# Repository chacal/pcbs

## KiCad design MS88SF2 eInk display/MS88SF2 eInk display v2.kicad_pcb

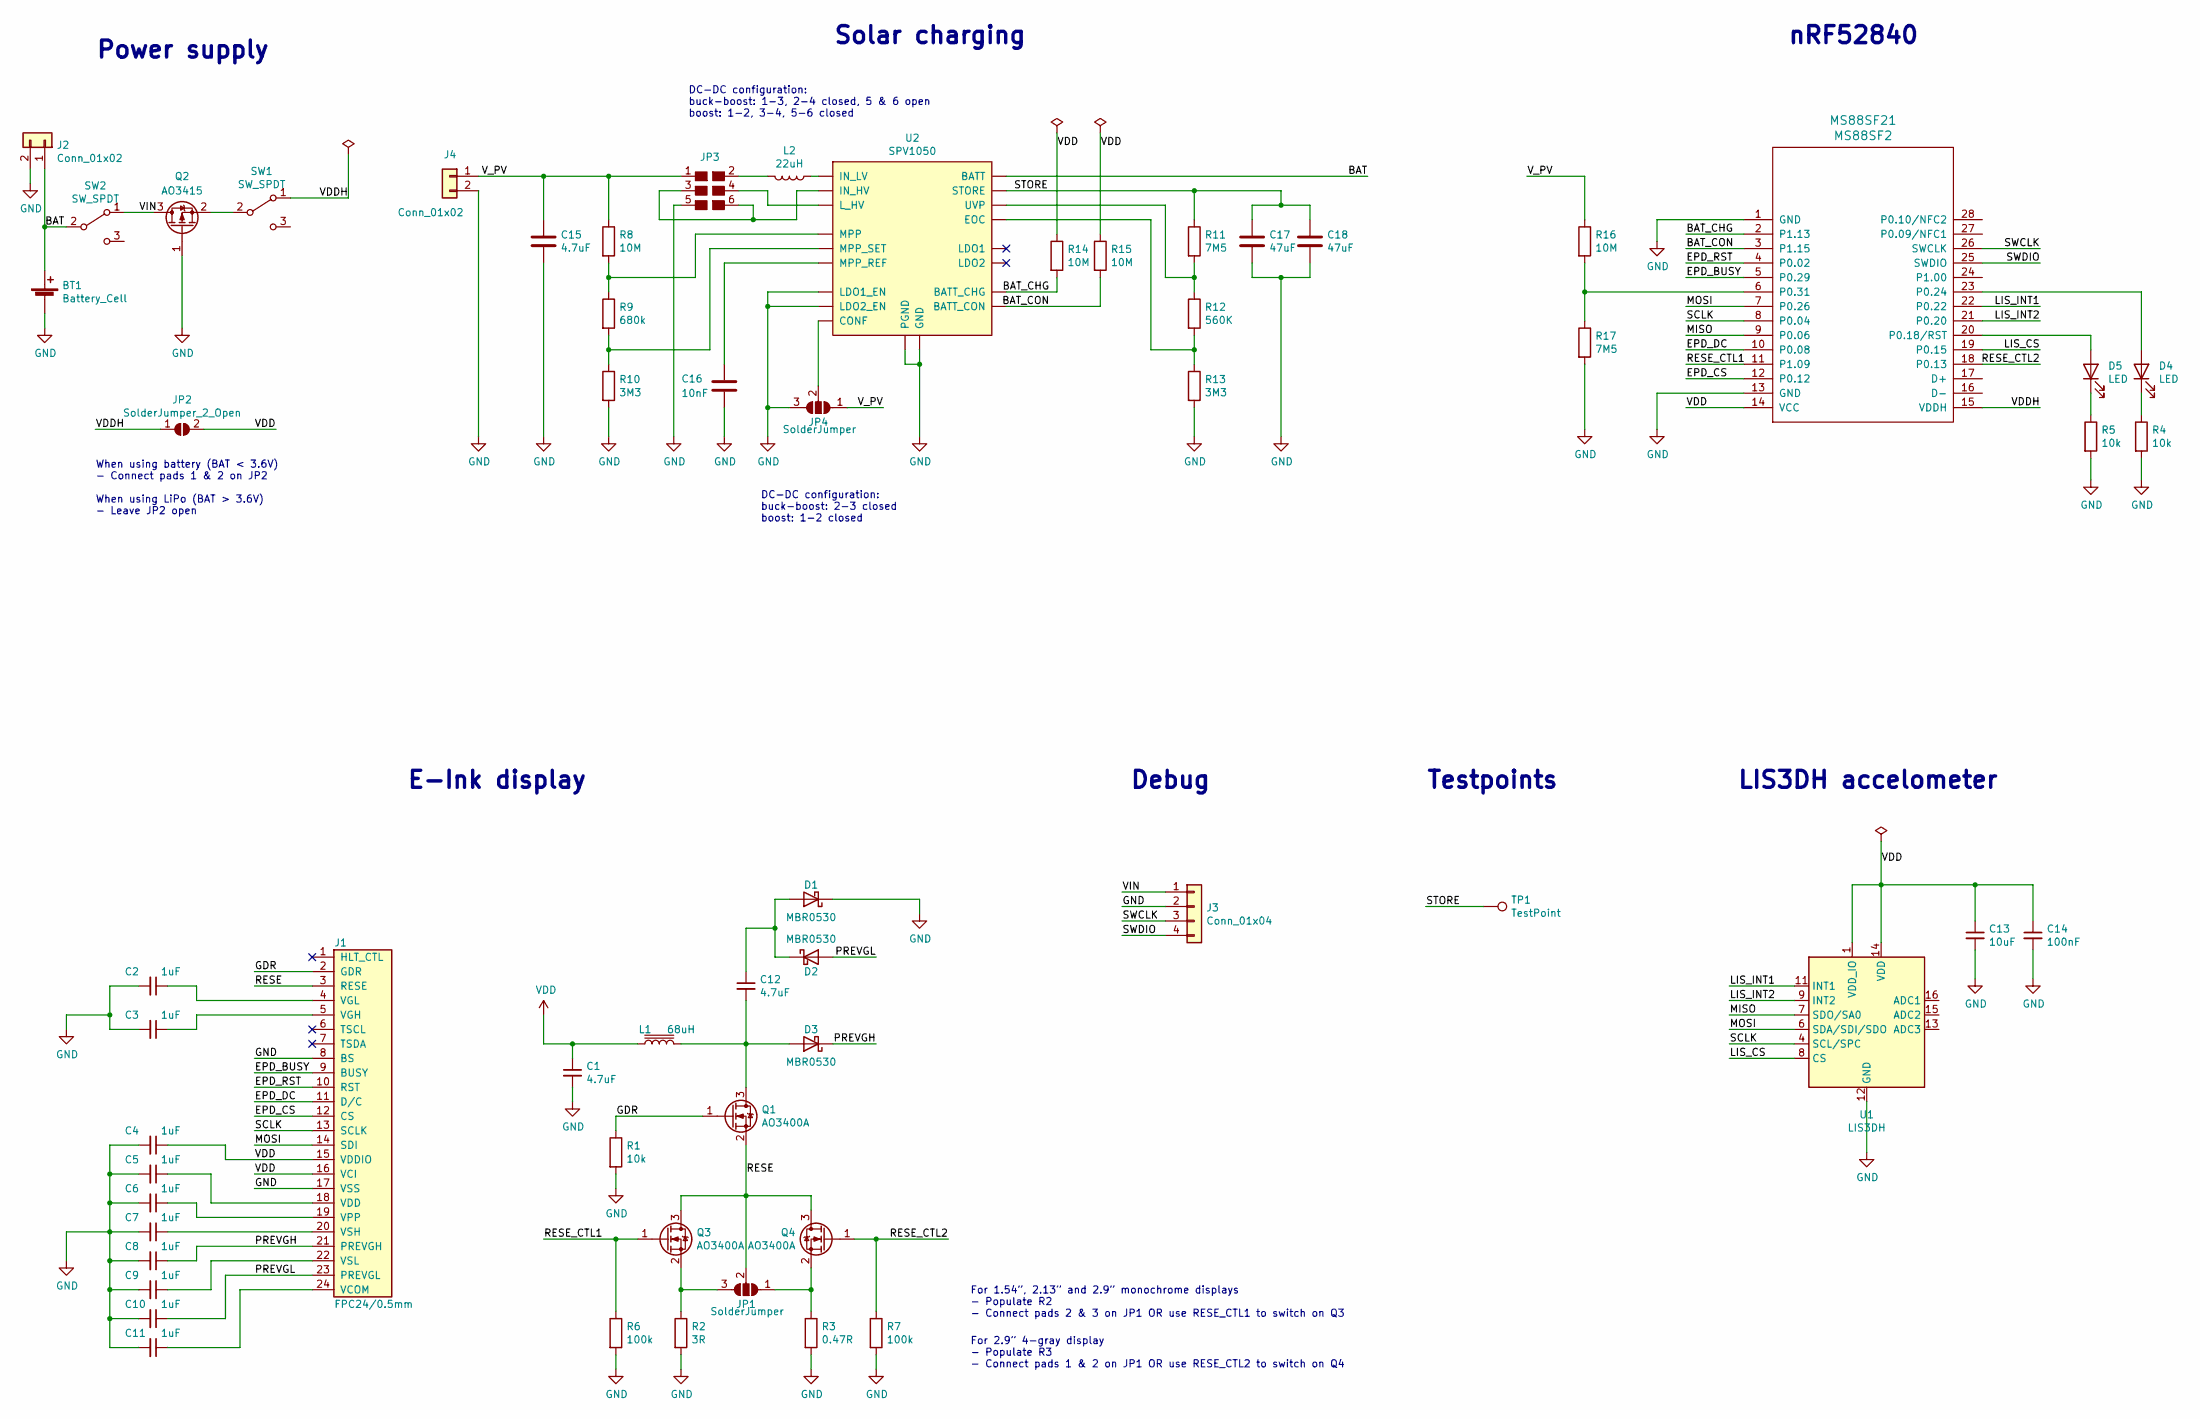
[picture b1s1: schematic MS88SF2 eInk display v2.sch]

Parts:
BT1: Battery_Cell; CR2032_holder
C1, C12, C15: 4.7uF; C_0805_2012Metric
C2, C3, C4, C5, C6, C7, C8, C9, C10, C11: 1uF; C_0805_2012Metric
C13: 10uF; CP_Elec_4x5.3
C14: 100nF; C_0805_2012Metric
C16: 10nF; C_0805_2012Metric
C17, C18: 47uF; C_0805_2012Metric
D1, D2, D3: MBR0530; D_SOD-123F
D4, D5: LED; LED_0805_2012Metric
J1: FPC24/0.5mm; FPC-24-0.50mm-top-contact
J2, J4: Conn_01x02; JST_PH_S2B-PH-K_1x02_P2.00mm_Horizontal
J3: Conn_01x04; PinSocket_1x04_P1.27mm_Vertical_SMD_Pin1Left
JP1, JP4: SolderJumper; SolderJumper-3_P1.3mm_Open_RoundedPad1.0x1.5mm
JP2: SolderJumper_2_Open; SolderJumper-2_P1.3mm_Open_RoundedPad1.0x1.5mm
JP3: SolderJumper_6_Bridged36; SolderJumper-6_P1.1mm_Open_Pad0.8x0.8mm
L1: 68uH; CD43
L2: 22uH; CD43
MS88SF21: MS88SF2
Q1, Q3, Q4: AO3400A; SOT-23
Q2: AO3415; SOT-23
R1: 10k; R_0603_1608Metric
R2: 3R; R_0603_1608Metric_Pad1.05x0.95mm_HandSolder
R3: 0.47R; R_0603_1608Metric
R4, R5: 10k; R_0603_1608Metric_Pad1.05x0.95mm_HandSolder
R6, R7: 100k; R_0603_1608Metric_Pad1.05x0.95mm_HandSolder
R8, R14, R15: 10M; R_0805_2012Metric
R9: 680k; R_0805_2012Metric
R10, R13: 3M3; R_0805_2012Metric
R11: 7M5; R_0805_2012Metric
R12: 560K; R_0805_2012Metric
R16: 10M; R_0603_1608Metric_Pad1.05x0.95mm_HandSolder
R17: 7M5; R_0603_1608Metric_Pad1.05x0.95mm_HandSolder
SW1, SW2: SW_SPDT; SW_SPDT_PCM12
TP1: TestPoint; TestPoint_Pad_D1.5mm
U1: LIS3DH; LGA-16_3x3mm_P0.5mm_3x5_hand_solder
U2: SPV1050; UQFN-20-1EP_3x3mm_P0.4mm_EP1.85x1.85mm_handsolder

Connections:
/BAT: BT1.1 (+), J2.1, SW2.2 (B), U2.14 (BATT)
/BAT_CHG: MS88SF21.2 (P1.13), R14.2, U2.7 (BATT_CHG)
/BAT_CON: MS88SF21.3 (P1.15), R15.2, U2.8 (BATT_CON)
/EPD_BUSY: J1.9 (BUSY), MS88SF21.5 (P0.29)
/EPD_CS: J1.12 (CS), MS88SF21.12 (P0.12)
/EPD_DC: J1.11 (D/C), MS88SF21.10 (P0.08)
/EPD_RST: J1.10 (RST), MS88SF21.4 (P0.02)
/GDR: J1.2 (GDR), Q1.1 (G), R1.1
/LIS_CS: MS88SF21.19 (P0.15), U1.8 (CS)
/LIS_INT1: MS88SF21.22 (P0.22), U1.11 (INT1)
/LIS_INT2: MS88SF21.21 (P0.20), U1.9 (INT2)
/MISO: MS88SF21.9 (P0.06), U1.7 (SDO/SA0)
/MOSI: J1.14 (SDI), MS88SF21.7 (P0.26), U1.6 (SDA/SDI/SDO)
/PREVGH: C8.1, D3.1 (K), J1.21 (PREVGH)
/PREVGL: C10.1, D2.2 (A), J1.23 (PREVGL)
/RESE: J1.3 (RESE), JP1.2 (C), Q1.2 (S), Q3.3 (D), Q4.3 (D)
/RESE_CTL1: MS88SF21.11 (P1.09), Q3.1 (G), R6.1
/RESE_CTL2: MS88SF21.18 (P0.13), Q4.1 (G), R7.1
/SCLK: J1.13 (SCLK), MS88SF21.8 (P0.04), U1.4 (SCL/SPC)
/STORE: C17.1, C18.1, R11.1, TP1.1, U2.15 (STORE)
/SWCLK: J3.3, MS88SF21.26 (SWCLK)
/SWDIO: J3.4, MS88SF21.25 (SWDIO)
/VDDH: JP2.1 (A), MS88SF21.15 (VDDH), SW1.1 (A)
/VIN: J3.1, Q2.3 (D), SW2.1 (A)
/V_PV: C15.1, J4.1, JP3.1, JP4.1 (A), R8.1, R16.1
GND: BT1.2 (-), C1.2, C2.2, C3.2, C4.2, C5.2, C6.2, C7.2, C8.2, C9.2, C10.2, C11.2, C13.2, C14.2, C15.2, C16.2, C17.2, C18.2, D1.1 (K), J1.8 (BS), J1.17 (VSS), J2.2, J3.2, J4.2, JP3.5, JP4.3 (B), MS88SF21.1 (GND), MS88SF21.13 (GND), Q2.1 (G), R1.2, R2.2, R3.2, R4.2, R5.2, R6.2, R7.2, R10.2, R13.2, R17.2, U1.5 (GND), U1.10 (GND), U1.12 (GND), U2.4 (GND), U2.5 (LDO1_EN), U2.6 (LDO2_EN), U2.18 (PGND)
unnamed: C2.1, J1.4 (VGL)
unnamed: C3.1, J1.5 (VGH)
unnamed: C5.1, J1.18 (VDD)
unnamed: C6.1, J1.19 (VPP)
unnamed: C7.1, J1.20 (VSH)
unnamed: C9.1, J1.22 (VSL)
unnamed: C11.1, J1.24 (VCOM)
unnamed: C12.1, D1.2 (A), D2.1 (K)
unnamed: C12.2, D3.2 (A), L1.2, Q1.3 (D)
unnamed: C16.1, U2.3 (MPP_REF)
unnamed: D4.1 (K), R4.1
unnamed: D4.2 (A), MS88SF21.23 (P0.24)
unnamed: D5.1 (K), R5.1
unnamed: D5.2 (A), MS88SF21.20 (P0.18/RST)
unnamed: JP1.1 (A), Q4.2 (S), R3.1
unnamed: JP1.3 (B), Q3.2 (S), R2.1
unnamed: JP3.2, L2.2
unnamed: JP3.3, JP3.6, U2.20 (IN_HV)
unnamed: JP3.4, U2.19 (L_HV)
unnamed: JP4.2 (C), U2.13 (CONF)
unnamed: L2.1, U2.16 (IN_LV)
unnamed: MS88SF21.6 (P0.31), R16.2, R17.1
unnamed: Q2.2 (S), SW1.2 (B)
unnamed: R8.2, R9.1, U2.1 (MPP)
unnamed: R9.2, R10.1, U2.2 (MPP_SET)
unnamed: R11.2, R12.1, U2.10 (UVP)
unnamed: R12.2, R13.1, U2.9 (EOC)
VDD: C1.1, C4.1, C13.1, C14.1, J1.15 (VDDIO), J1.16 (VCI), JP2.2 (B), L1.1, MS88SF21.14 (VCC), R14.1, R15.1, U1.1 (VDD_IO), U1.14 (VDD)

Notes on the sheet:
For 2.9” 4-gray display - Populate R3 - Connect pads 1 & 2 on JP1 OR use RESE_CTL2 to switch on Q4
For 1.54”, 2.13” and 2.9” monochrome displays - Populate R2 - Connect pads 2 & 3 on JP1 OR use RESE_CTL1 to switch on Q3
When using battery (BAT < 3.6V) - Connect pads 1 & 2 on JP2 When using LiPo (BAT > 3.6V) - Leave JP2 open
LIS3DH accelometer
Testpoints
nRF52840
E-Ink display
Debug
Power supply
DC-DC configuration: buck-boost: 1-3, 2-4 closed, 5 & 6 open boost: 1-2, 3-4, 5-6 closed
DC-DC configuration: buck-boost: 2-3 closed boost: 1-2 closed
Solar charging

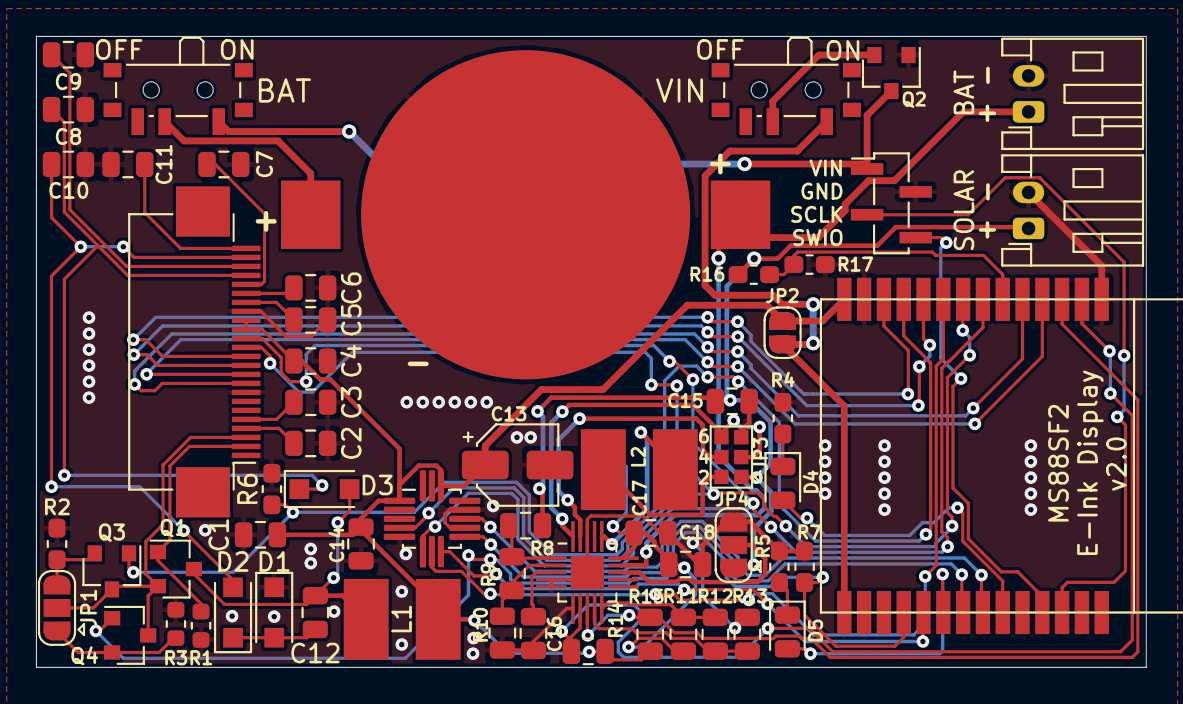
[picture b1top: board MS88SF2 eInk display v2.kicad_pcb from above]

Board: 2 copper layers, 61.7 x 35.1 mm, 61 parts (1 on the bottom side), 54 nets.

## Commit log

2021-03-07 Add MS88SF2 e-ink display
